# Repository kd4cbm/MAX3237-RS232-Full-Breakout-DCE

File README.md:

# MAX3237 Full Breakout Board (DCE)

A 2-layer breakout board that converts a 3.3V TTL UART into true RS-232 levels
using the [Maxim/TI MAX3237](https://www.analog.com/media/en/technical-documentation/data-sheets/max3222-max3241.pdf),
wired as **DCE** (modem-side) so it plugs directly into a DTE (terminal/PC)
with a standard straight-through DE-9 cable. Built as the RS-232 front end
for the [RetroWiFiModem](https://github.com/kd4cbm/Zimodem-VFD) project's
ESP32-S3 port, but usable standalone anywhere a 3.3V-logic device needs a
real RS-232 port.

## ⚠ Known issue in previously-manufactured boards: J2 footprint was rotated 180°

Boards ordered from `main` **before this fix** have the J2 DE-9 footprint
rotated 180° from correct relative to the schematic - both left-right *and*
which physical row (the 5-pin row vs. the 4-pin row) sits nearer the board
edge are affected. The pads and copper are internally consistent with each
other and with the net names below, but the physical pin layout does not
match the standard DE-9 pinout - if you plug a straight-through cable into
an affected board, you will connect to the wrong signal on every pin except
5 (GND, which sits on the connector's center axis).

This shipped in two stages. An initial fix (commit `0a0792f`) corrected the
left-right pin order, verified at the time against KiCad's own standard
`Connector_Dsub` library footprint - but that check only compared left-right
order and missed that the two pin rows were *also* swapped front-to-back, so
boards built from that revision alone still had the 5-pin row nearer the
board edge instead of the 4-pin row. That was caught on a second, closer
comparison against the same trusted footprint (this time checking full 2-D
pad geometry, not just left-right rank) and against the actual net-name
silkscreen labels, and is corrected as of commit `1042daa` - J2 rotated the
remaining 180°, all copper ripped and rerouted again.

**If you already have a board built from `main` before this revision** -
whether it predates the first fix or only the second - do not assume the J2
pins match the table below. Either replace the board with one built from
this revision, or trace out each pin with a meter against the
schematic/netlist and build a corrected cable or adapter for that specific
board before relying on it.

A related but separate defect existed only in git history, never manufactured:
commit `1042daa`'s row-orientation fix moved the J2 *pads* to the correct
physical location but repositioned the *silkscreen net labels* using a wrong
assumption about which pad number carried which net, so 8 of the 9 printed
labels ended up swapped with their opposite-row counterpart (e.g. the pad
that actually carries DCD was labeled "GND", and vice versa) - the copper
and nets themselves were correct the whole time, only the printed text was
wrong. Fixed as of the current revision; the silkscreen now matches the
[J2 pinout](#connectors) below pin-for-pin.

## Connectors

**J1 - TTL header** (10-pin, 2.54mm, 3.3V logic side)

| Pin | 1 | 2 | 3 | 4 | 5 | 6 | 7 | 8 | 9 | 10 |
|---|---|---|---|---|---|---|---|---|---|---|
| Signal | DCD | RXD | TXD | DTR | GND | DSR | RTS | CTS | RI | VCC |

**J2 - DE-9 female** (RS-232 side, DCE pinout - wire straight through to a DTE)

Standard DE-9 DCE pinout: DCD(1), RXD(2), TXD(3), DTR(4), GND(5), DSR(6),
RTS(7), CTS(8), RI(9).

## Function jumpers

Each jumper is a 3-pin header: pin 1 (square pad) = +3.3V, pin 3 (round pad)
= GND, pin 2/center = the signal. Bridge pins 1-2 or 2-3 with a shunt to pick
a state.

| Jumper | Function | VCC position | GND position |
|---|---|---|---|
| J3 | MBAUD (data rate select) | MegaBaud mode, up to 1Mbps | Normal mode, up to 250kbps |
| J4 | EN&#772; (receiver enable, active-low) | Receivers disabled (high-Z) | Receivers enabled (normal) |
| J5 | SHDN&#772; (shutdown, active-low) | Normal operation | Shutdown, <1uA supply current |

## Capacitors

Per the MAX3237 datasheet's Table 2, worst-case row (VCC = 3.3V &plusmn;10%):

- **C1, C2, C3, C4** - 0.22uF, charge-pump/reservoir caps
- **C5** - 0.1uF, VCC bypass (the standard smaller bypass value, independent
  of the charge-pump table)

All five are 0805 ceramic MLCC. See [Assembly](#assembly-jlcpcb-pcba) for
sourcing notes.

## Board

- 2-layer, 31.75 x 41.93mm, JLCPCB-manufacturable (checked against their
  published capabilities: trace/clearance, via annular ring &ge;0.18mm,
  silkscreen &ge;1.0mm/0.15mm, hole-to-hole spacing, copper-to-edge)
- GND poured on both copper layers
- Two M3 mounting holes, X-aligned with the DE-9 connector's own built-in
  mounting/jackscrew posts so both hole pairs share one centerline
- Keepout zones around all four plated mounting holes (the 2 board holes +
  the DE-9's own 2 hardware holes) so a copper pour can't bridge to a
  grounded chassis screw
- Routed with [Freerouting](https://github.com/freerouting/freerouting) 2.3.0

## Assembly (JLCPCB PCBA)

This board is set up for **SMD-only PCBA**: JLCPCB places U1 and C1-C5 (all
SMD); the DE-9 socket, TTL header, and 3 jumpers are through-hole and ship
loose for hand-soldering afterward - they're simple, forgiving parts to
solder by hand, and this keeps assembly cost and lead time down versus
sourcing THT parts for machine placement.

Files in [`hardware/`](hardware/):

- `kicad/` - full KiCad 10 project (schematic + PCB)
- `gerbers/Gerbers_*.zip` - Gerber + Excellon drill files, ready to upload. **This zip is a generated
  snapshot, not kept in sync automatically** - it sat stale from rev 4 through rev 8 while the PCB
  source moved on. Regenerate it (`kicad-cli pcb export gerbers` + `pcb export drill`) any time
  `hardware/kicad/*.kicad_pcb` changes, before ordering
- `CPL_SMD.csv` - placement/position file (SMD parts only)
- `BOM_PCBA_JLCPCB.csv` - PCBA bill of materials (SMD parts only). U1's LCSC
  part number (`C2671155`, MAX3237EIPWR) is verified against LCSC's own
  listing. The capacitor rows intentionally list full specs (0805, X7R,
  value, &ge;16V) with **no** LCSC number - JLCPCB's basic-parts catalog is a
  live, dynamic search that isn't reliably scriptable, and these are common
  enough values that matching one at checkout takes seconds. Verify current
  stock/pricing before ordering rather than trusting a number pinned months
  earlier.
- `BOM_full.csv` - every part on the board, including the through-hole
  connectors, for your own reference/hand-assembly shopping list

**Before ordering, check U1's orientation in JLCPCB's assembly preview.**
`CPL_SMD.csv` currently has U1 at rotation 180, verified against JLCPCB's
own preview tool - but this value depends on which specific LCSC library
part they match to the MAX3237EIPWR footprint (`C2671155`), and that
match/library entry can change over time. If U1 looks rotated in their
preview, JLCPCB's placement review UI lets you rotate a part directly and
save the correction - no need to regenerate any files for a one-off order.
A quick way to confirm correct placement without knowing the datasheet by
heart: pin 1 is on the net `/MAX-C2+`, i.e. it should land right next to
**C2**'s own pad (not C4, and not on the opposite pin row).

## Revision history

| Rev | Notes |
|---|---|
| 0 | Original layout, master reference |
| 1 | Pre-routing checkpoint (placement + keepouts finalized) |
| 2 | Post-routing checkpoint (Freerouting output, traces only) |
| 3 | Added GND pour, widened VCC traces |
| 4 | JLCPCB via/silkscreen compliance fixes, RXD/TXD silkscreen wording |
| 5 | Partial fix for mirrored J2 (DE-9) footprint - corrected left-right pin order only; row-to-edge assignment was still wrong (see rev 6) |
| 6 | Completed the J2 (DE-9) footprint fix: rotated the remaining 180° so the 4-pin row is nearer the board edge; full copper rip/reroute/repour; see [Known issue](#-known-issue-in-previously-manufactured-boards-j2-footprint-was-rotated-180) above |
| 7 | Cleared two starved-thermal DRC warnings (J2/J3 GND pads set to solid zone connection); no pad or copper changes |
| 8 | Full copper rip/reroute/repour (no pad changes) to clean up scattered clearance-void shapes left by earlier auto-routes; added a dedicated `Power` net class so `+3.3V` routes at 0.4mm instead of the 0.2mm signal-trace default |
| 9 | Regenerated `gerbers/Gerbers_*.zip` and the drill file, which had never been updated past rev 4 - anyone ordering from the old zip would have gotten the original mirrored-J2 board regardless of every PCB-source fix above. Verified against the drill file directly: the 4-pin row's holes now fall closer to the board edge than the 5-pin row's, and every component-hole count (J1/J2/J3-5 pads, both mounting-hole types) matches the pre-fix file exactly - only the via count differs, as expected from a fresh autoroute. `CPL_SMD.csv` and the BOM files were checked and are still correct as-is (no SMD part moved or changed value) |
| 10 | **Current** - Fixed J2's silkscreen net labels: 8 of the 9 (every one but TXD, which sits on the axis of symmetry) were mirror-swapped with their opposite-row counterpart, a mistake introduced when the labels were repositioned during the rev 6 row-orientation fix - the *pads* moved to the correct physical location then, but the labels were repositioned using a wrong net-to-pad-number assumption - the silkscreen now matches the [J2 pinout](#connectors) above pin-for-pin. No copper/pad changes; Gerbers and drill regenerated since the silkscreen layer changed |

## License

Hardware design files (schematic, PCB, Gerbers) are released under
[CERN-OHL-W v2](https://cern-ohl.web.cern.ch/) - a weakly-reciprocal open
hardware license: you're free to use, modify, and manufacture this design,
including commercially; modifications to these design files themselves stay
open, but boards built from them (or your own separate designs that merely
use this one) don't inherit that obligation. See [LICENSE](LICENSE).

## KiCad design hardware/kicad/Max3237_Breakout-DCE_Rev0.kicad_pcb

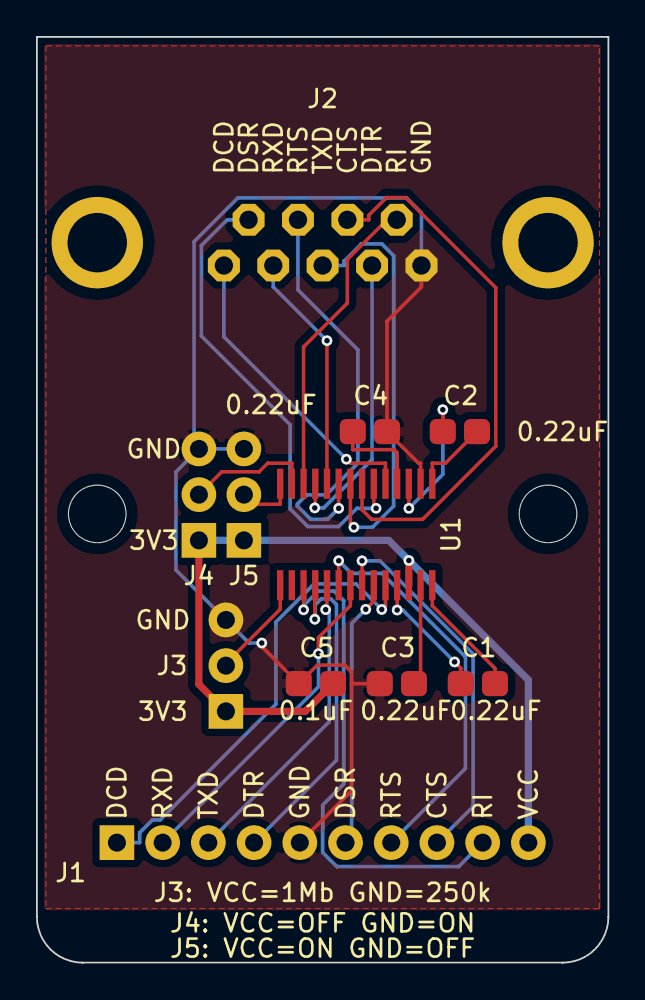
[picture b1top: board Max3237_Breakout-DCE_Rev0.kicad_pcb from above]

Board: 2 copper layers, 31.8 x 51.4 mm, 13 parts (0 on the bottom side), 27 nets.

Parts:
C1, C2, C3, C4: 0.22uF; C_0805_2012Metric
C5: 0.1uF; C_0805_2012Metric
J1: TTL_HEADER; Header_1x10_P2.54mm_Round
J2: DE9_RS232; DE9_Female_THT
J3: MBAUD; Jumper_1x03_P2.54mm_Round
J4: ENABLE; Jumper_1x03_P2.54mm_Round
J5: SHUTDOWN; Jumper_1x03_P2.54mm_Round
MH1, MH2: MountingHole; MountingHole_3.2mm_M3
U1: MAX3237EIPWR; PW28

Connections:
+3.3V: C5.1, J1.10, J3.1, J4.1, J5.1, U1.26
/MAX-C1+: C1.1, U1.28
/MAX-C1-: C1.2, U1.25
/MAX-C2+: C2.1, U1.1
/MAX-C2-: C2.2, U1.3
/MAX-EN: J4.2, U1.13
/MAX-MBAUD: J3.2, U1.15
/MAX-SHDN: J5.2, U1.14
/MAX-V+: C3.1, U1.27
/MAX-V-: C4.2, U1.4
/RS232-CTS: J2.8, U1.7
/RS232-DCD: J2.1, U1.5
/RS232-DSR: J2.6, U1.6
/RS232-DTR: J2.4, U1.11
/RS232-RI: J2.9, U1.12
/RS232-RTS: J2.7, U1.9
/RS232-RXD: J2.2, U1.10
/RS232-TXD: J2.3, U1.8
/TTL-CTS: J1.8, U1.22
/TTL-DCD: J1.1, U1.24
/TTL-DSR: J1.6, U1.23
/TTL-DTR: J1.4, U1.18
/TTL-RI: J1.9, U1.17
/TTL-RTS: J1.7, U1.20
/TTL-RXD: J1.2, U1.21
/TTL-TXD: J1.3, U1.19
GND: C3.2, C4.1, C5.2, J1.5, J2.5, J3.3, J4.3, J5.3, U1.2

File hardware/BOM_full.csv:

"Designator","Value","Footprint","Qty"
"C1-C4","0.22uf","Capacitor_SMD:C_0805_2012Metric","4"
"C5","0.1uf","Capacitor_SMD:C_0805_2012Metric","1"
"J1","Conn_01x10","Connector_PinHeader_2.54mm:PinHeader_1x10_P2.54mm_Vertical","1"
"J2","DE9_Socket","Connector_Dsub:DSUB-9_Socket_Horizontal_P2.77x2.84mm_EdgePinOffset9.40mm","1"
"J3","MBAUD","Connector_PinHeader_2.54mm:PinHeader_1x03_P2.54mm_Vertical","1"
"J4","ENABLE","Connector_PinHeader_2.54mm:PinHeader_1x03_P2.54mm_Vertical","1"
"J5","SHUTDOWN","Connector_PinHeader_2.54mm:PinHeader_1x03_P2.54mm_Vertical","1"
"U1","MAX3237EIPWR","MAX3237:PW28","1"
